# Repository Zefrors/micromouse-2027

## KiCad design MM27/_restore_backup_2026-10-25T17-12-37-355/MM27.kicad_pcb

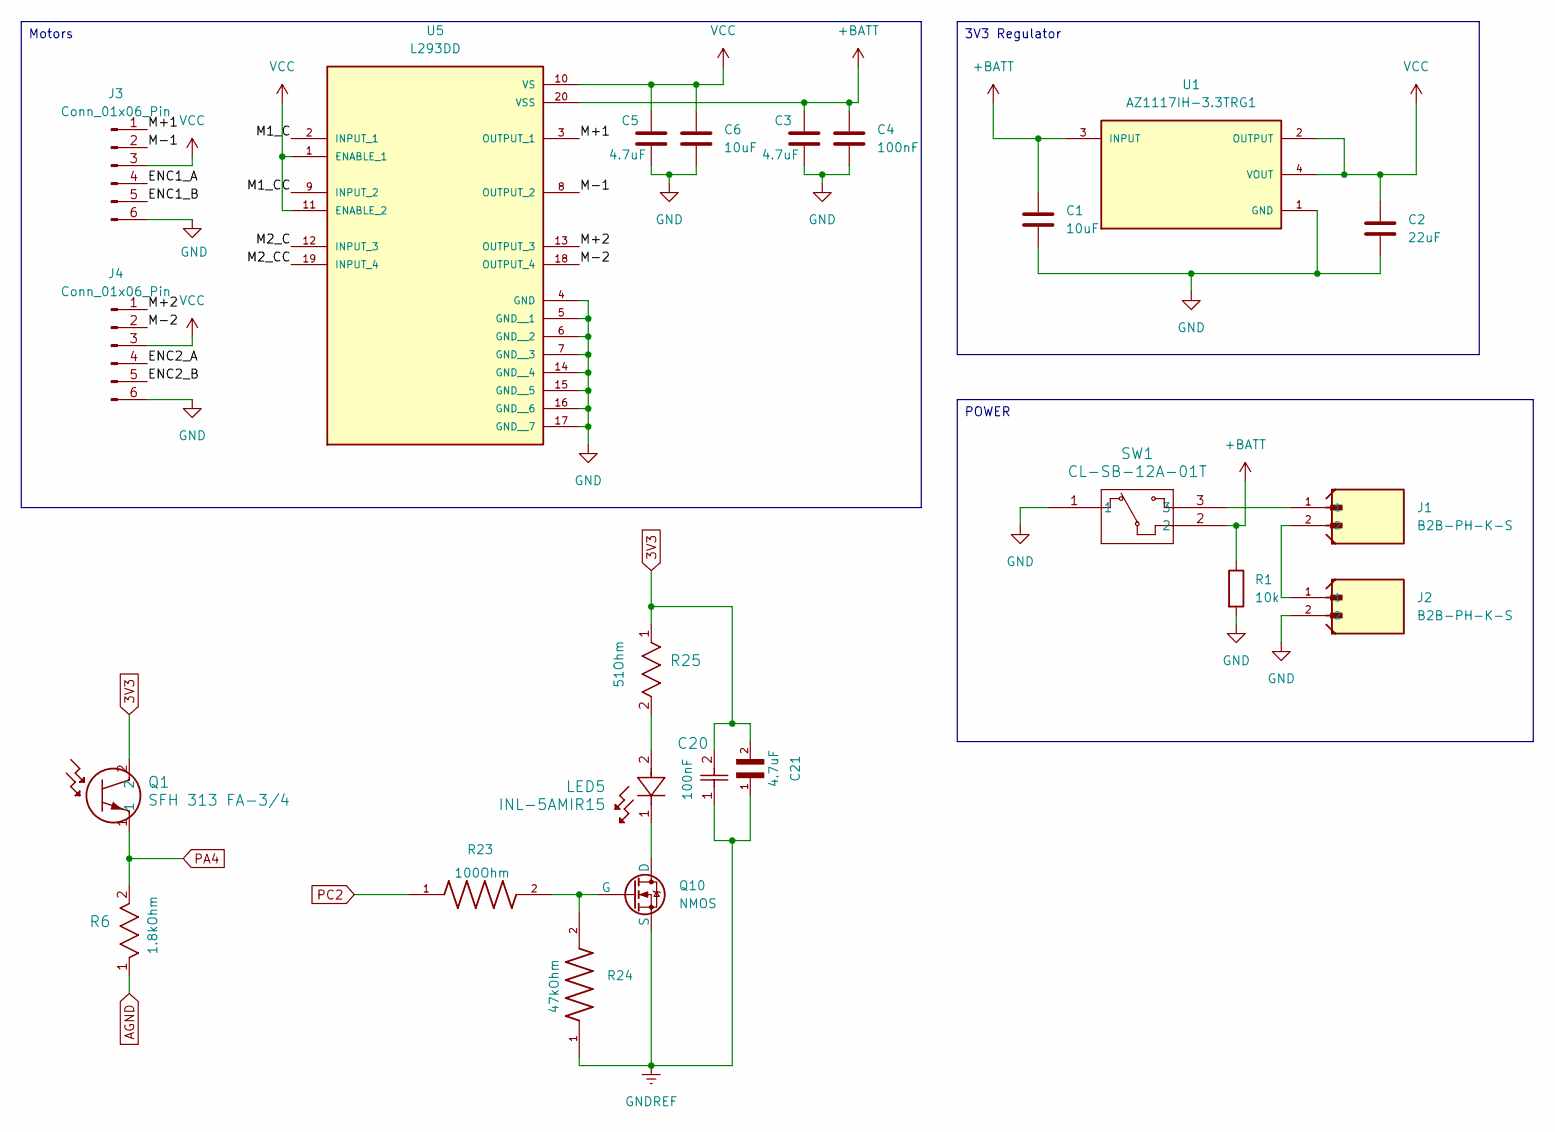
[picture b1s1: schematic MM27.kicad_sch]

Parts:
C1, C6: 10uF; C_0805_2012Metric_Pad1.18x1.45mm_HandSolder
C2: 22uF; C_0805_2012Metric_Pad1.18x1.45mm_HandSolder
C3, C5: 4.7uF; C_0805_2012Metric_Pad1.18x1.45mm_HandSolder
C4: 100nF; C_0805_2012Metric_Pad1.18x1.45mm_HandSolder
C20: CL21B104KBCNNNC; C_0805_2012Metric
C21: CL21A475KAQNNNE; C_0805_2012Metric
J1, J2: B2B-PH-K-S; JST_B2B-PH-K-S
J3, J4: Conn_01x06_Pin; JST_SH_BM06B-SRSS-TB_1x06-1MP_P1.00mm_Vertical
LED5: INL-5AMIR15; LED_D3.0mm
Q1: SFH 313 FA-3/4; LED_D3.0mm
Q10: NMOS; SOT-23
R1: 10k; R_0805_2012Metric_Pad1.20x1.40mm_HandSolder
R6: RMCF0805JT1K80; R_0805_2012Metric
R23: ERJ-6GEYJ101V; R_0805_2012Metric; PARTREV 3/1/2020
R24: RMCF0805JT47K0; R_0805_2012Metric
R25: RC0805FR-0751RL; R_0805_2012Metric
SW1: CL-SB-12A-01T; CL-SB-12A-01T_NDC
U1: AZ1117IH-3.3TRG1; SOT230P700X185-4N; PARTREV 2-2
U5: L293DD; SOIC127P1032X265-20N; PARTREV N/A

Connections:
3V3: C20.2, C21.2, Q1.2, R25.1
+BATT: C1.1, C3.1, C4.1, R1.1, SW1.2, U1.3 (INPUT), U5.20 (VSS)
/ENC1_A: J3.4
/ENC1_B: J3.5
/ENC2_A: J4.4
/ENC2_B: J4.5
/M1_C: U5.2 (INPUT_1)
/M1_CC: U5.9 (INPUT_2)
/M2_C: U5.12 (INPUT_3)
/M2_CC: U5.19 (INPUT_4)
/M+1: J3.1, U5.3 (OUTPUT_1)
/M+2: J4.1, U5.13 (OUTPUT_3)
/M-1: J3.2, U5.8 (OUTPUT_2)
/M-2: J4.2, U5.18 (OUTPUT_4)
AGND: R6.1
GND: C1.2, C2.2, C3.2, C4.2, C5.2, C6.2, J2.2, J3.6, J4.6, R1.2, SW1.1, U1.1 (GND), U5.4 (GND), U5.5 (GND__1), U5.6 (GND__2), U5.7 (GND__3), U5.14 (GND__4), U5.15 (GND__5), U5.16 (GND__6), U5.17 (GND__7)
GNDREF: C20.1, C21.1, Q10.3 (S), R24.1
unnamed: J1.1, SW1.3
unnamed: J1.2, J2.1
unnamed: LED5.2, R25.2
unnamed: LED5.1, Q10.1 (D)
unnamed: Q10.2 (G), R23.2, R24.2
PA4: Q1.1, R6.2
PC2: R23.1
VCC: C2.1, C5.1, C6.1, J3.3, J4.3, U1.2 (OUTPUT), U1.4 (VOUT), U5.1 (ENABLE_1), U5.10 (VS), U5.11 (ENABLE_2)

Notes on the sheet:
Motors
POWER
3V3 Regulator

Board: 2 copper layers, 23 parts (0 on the bottom side), 15 nets, no tracks yet.
